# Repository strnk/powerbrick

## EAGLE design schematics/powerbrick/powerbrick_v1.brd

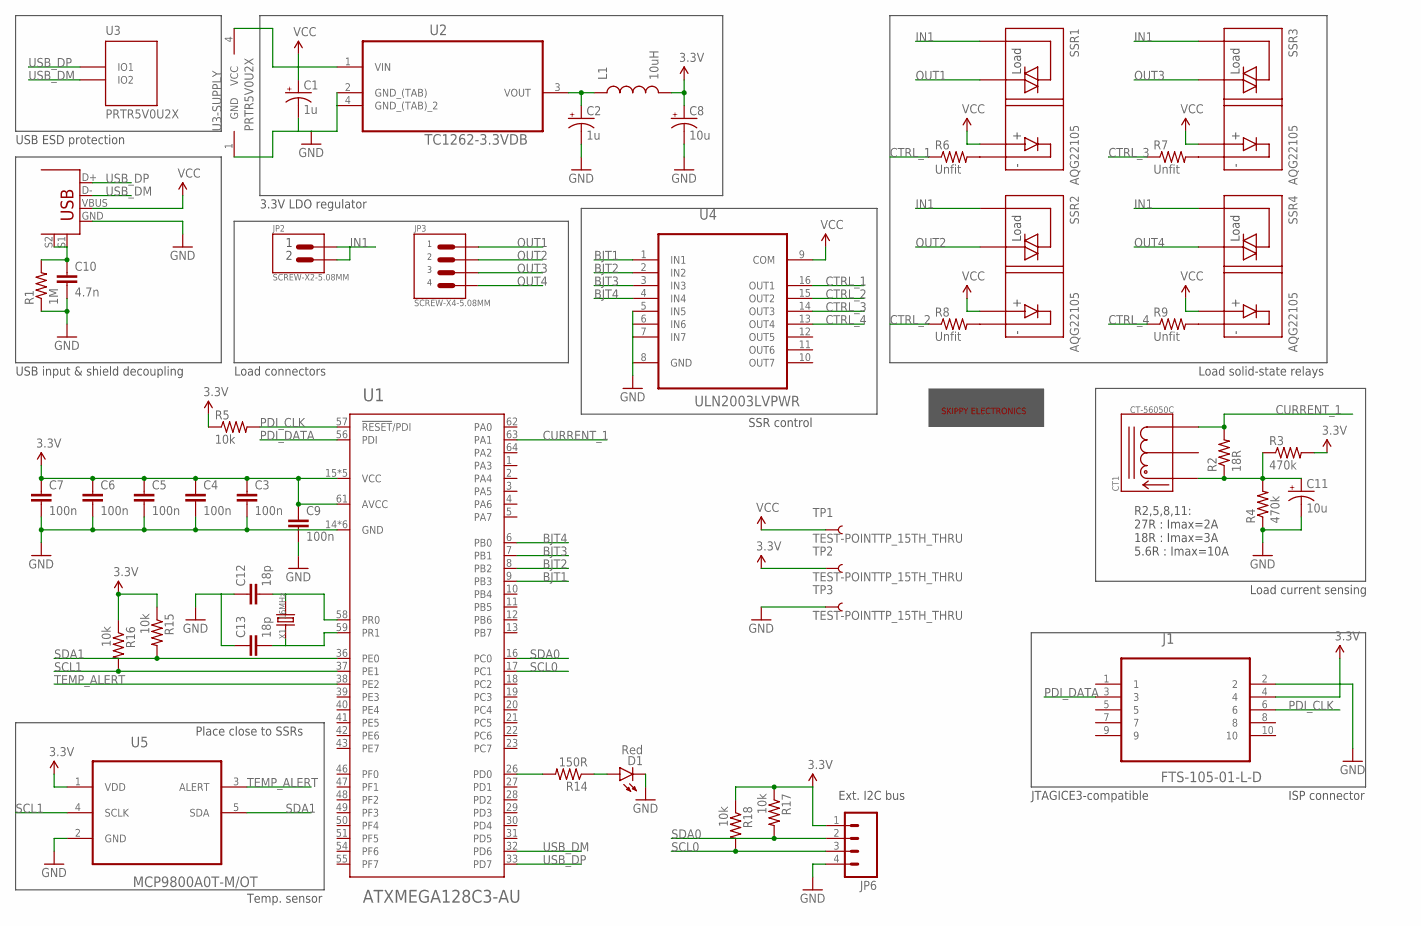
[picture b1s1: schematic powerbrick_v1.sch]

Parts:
C1, C2: 1u; EIA3216-KIT
C3, C4, C5, C6, C7, C9: 100n; 0805
C8, C11: 10u; EIA3216-KIT
C10: 4.7n; 0805
C12, C13: 18p; 0805
CT1: CT-56050C
D1: Red; LED5MM
J1: FTS-105-01-L-D; SAMTEC_FTS-105-01-L-D
JP1: USB+SHIELD; USB-B-PTH
JP2: SCREW-X2-5.08MM; 1X02-5.08MM
JP3: SCREW-X4-5.08MM; 1X04
JP6: M04POLAR_LOCK; MOLEX-1X4_LOCK
L1: 10uH; SRN6045
R1: 1M; 0805
R2: 18R; R2512
R3, R4: 470k; 0805
R5, R15, R16, R17, R18: 10k; 0805
R6, R7, R8, R9: Unfit; 0805
R14: 150R; 0805
SSR1, SSR2, SSR3, SSR4: AQG22105; SSR-100-400-300
TP1, TP2, TP3: TEST-POINTTP_15TH_THRU; TP_15TH
U1: ATXMEGA128C3-AU; TQFP-64A-64
U2: TC1262-3.3VDB; SOT230P700X180-4N
U3: PRTR5V0U2X; SOT-143B
U4: ULN2003LVPWR; SOP65P640X120-16N
U5: MCP9800A0T-M/OT; SOT95P280X145-5N
U$2: SKIPPYTXT-PLC-10MM
X1: 16MHz; HC49S

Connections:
3.3V: C3.1, C4.1, C5.1, C6.1, C7.1, C8.A (+), C9.1, J1.4, JP6.1, L1.2, R3.2, R5.1, R15.1, R16.1, R17.1, R18.1, TP2.P$1, U1.15 (VCC), U1.25 (VCC), U1.35 (VCC), U1.45 (VCC), U1.53 (VCC), U1.61 (AVCC), U5.1 (VDD)
BJT1: U1.9 (PB3), U4.1 (IN1)
BJT2: U1.8 (PB2), U4.2 (IN2)
BJT3: U1.7 (PB1), U4.3 (IN3)
BJT4: U1.6 (PB0), U4.4 (IN4)
CTRL_1: R6.1, U4.16 (OUT1)
CTRL_2: R8.1, U4.15 (OUT2)
CTRL_3: R7.1, U4.14 (OUT3)
CTRL_4: R9.1, U4.13 (OUT4)
CURRENT_1: CT1.P$3, R2.2, U1.63 (PA1)
GND: C1.C (-), C2.C (-), C3.2, C4.2, C5.2, C6.2, C7.2, C8.C (-), C9.2, C10.2, C11.C (-), C12.1, C13.1, D1.K (C), J1.2, JP1.GND, JP6.4, R1.1, R4.1, TP3.P$1, U1.14 (GND), U1.24 (GND), U1.34 (GND), U1.44 (GND), U1.52 (GND), U1.60 (GND), U2.2 (GND_(TAB)), U2.4 (GND_(TAB)_2), U3.1 (GND), U4.5 (IN5), U4.6 (IN6), U4.7 (IN7), U4.8 (GND), U5.2 (GND)
IN1: JP2.P$1, JP2.P$2, SSR1.P$4, SSR2.P$4, SSR3.P$4, SSR4.P$4
unnamed: C12.2, U1.58 (PR0), X1.2
unnamed: C2.A (+), L1.1, U2.3 (VOUT)
unnamed: C13.2, U1.59 (PR1), X1.1
unnamed: C11.A (+), CT1.P$1, R2.1, R3.1, R4.2
unnamed: C10.1, JP1.S1, JP1.S2, R1.2
unnamed: R6.2, SSR1.P$1
unnamed: R7.2, SSR3.P$1
unnamed: R9.2, SSR4.P$1
unnamed: R14.2, U1.26 (PD0)
unnamed: D1.A, R14.1
unnamed: R8.2, SSR2.P$1
OUT1: JP3.P$1, SSR1.P$3
OUT2: JP3.P$2, SSR2.P$3
OUT3: JP3.P$3, SSR3.P$3
OUT4: JP3.P$4, SSR4.P$3
PDI_CLK: J1.6, R5.2, U1.57 (!RESET!/PDI)
PDI_DATA: J1.3, U1.56 (PDI)
SCL0: JP6.3, R18.2, U1.17 (PC1)
SCL1: R16.2, U1.37 (PE1), U5.4 (SCLK)
SDA0: JP6.2, R17.2, U1.16 (PC0)
SDA1: R15.2, U1.36 (PE0), U5.5 (SDA)
TEMP_ALERT: U1.38 (PE2), U5.3 (ALERT)
USB_DM: JP1.D-, U1.32 (PD6), U3.3 (IO2)
USB_DP: JP1.D+, U1.33 (PD7), U3.2 (IO1)
VCC: C1.A (+), JP1.VBUS, SSR1.P$2, SSR2.P$2, SSR3.P$2, SSR4.P$2, TP1.P$1, U2.1 (VIN), U3.4 (VCC), U4.9 (COM)

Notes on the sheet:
USB ESD protection
USB input & shield decoupling
3.3V LDO regulator
Load connectors
Load solid-state relays
R2,5,8,11: 27R : Imax=2A 18R : Imax=3A 5.6R : Imax=10A
Load current sensing
Temp. sensor
Place close to SSRs
Ext. I2C bus
SSR control
ISP connector
JTAGICE3-compatible

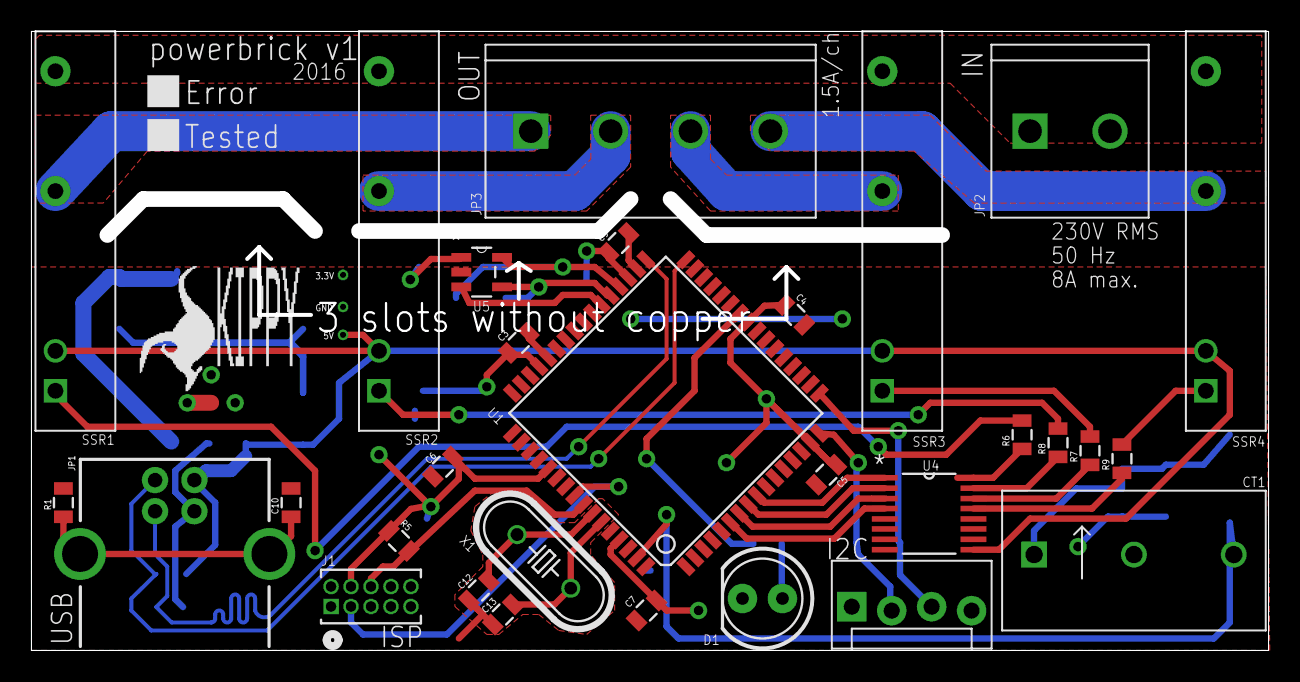
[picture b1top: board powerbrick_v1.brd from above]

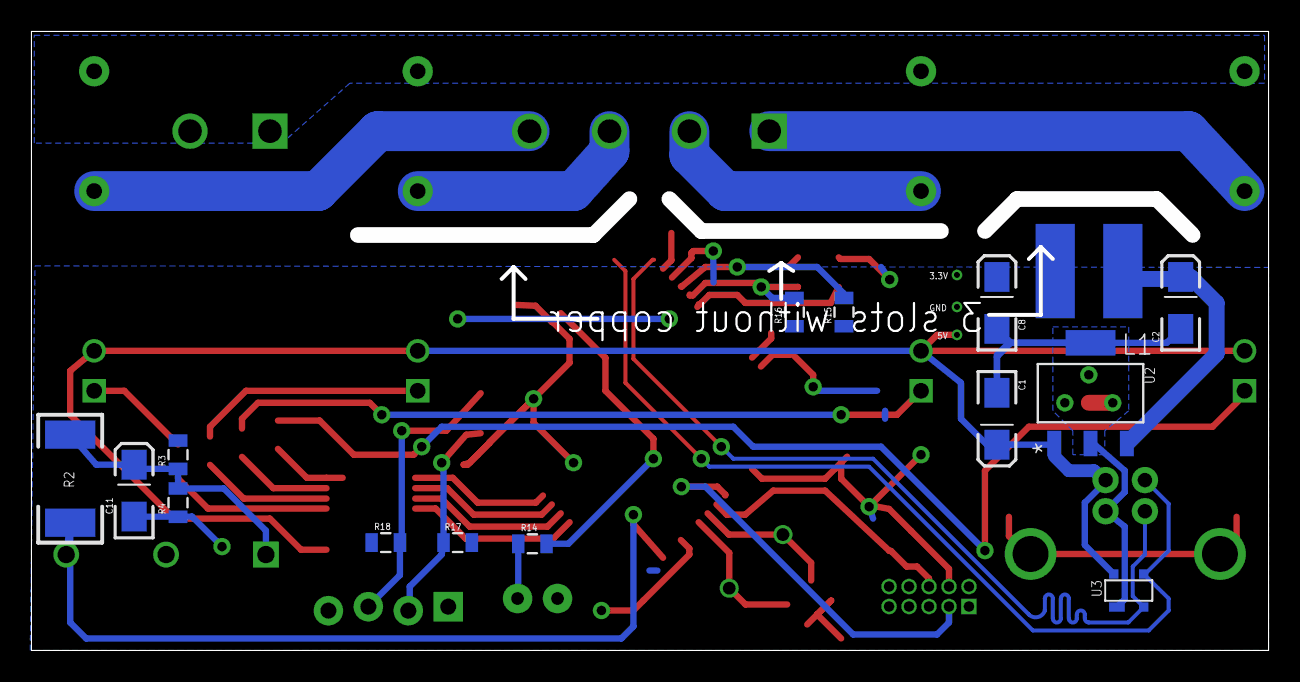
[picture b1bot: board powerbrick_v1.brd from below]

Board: 4 copper layers, 77.7 x 38.4 mm, 49 parts (15 on the bottom side), 37 nets.

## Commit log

2013-12-21 SeeedStudio libraries and motherboard schematic draft
2013-12-21 New STM32F405RGT symbol in stm32 lib
2014-01-06 Eagle library of Skippy logos
2015-02-07 Eagle lib update & logos
2015-02-08 Added Sparkfun Eagle libs
2015-02-08 Moved Sparkfun lib to 3rd-party
2015-02-08 Reorganized libs, added DC/DC buck converter and power board
2015-02-08 Inductor lib and powerboard 5V rail
2015-02-09 Power board finalized
2015-02-11 New PCB for power board
2015-02-19 Lower resolution logo for Gerber export
2015-05-03 Motherboard reference design
2015-05-04 Library refactor and motherboard update
2015-05-04 Bluetooth debug module and external boards lib. Motherboard update
2015-05-08 Motherboard v1 RTM
2016-04-06 Added 3rd-party seeedstudio and sparkfun libs
2016-04-06 Powerbrick schematic
2016-04-07 Additional docs
2016-04-07 Git ignore file
2016-04-07 Libs and drawing update
2016-04-09 Current transformer doc
2016-04-09 New parts
2016-04-09 Powerbrick schematic update
2016-04-12 Schematics update
2016-04-17 Added ISP header
2016-04-18 Replaced ISP connector - PCB draft
2016-04-19 Added test points and HV separation milling
2016-04-22 Added slots to separate power planes from mains voltage traces
2016-04-22 Powerbrick v1 RTM

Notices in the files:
parts and their libraries:
SparkFun-Connectors: Licensing: Creative Commons ShareAlike 4.0 International - https://creativecommons.org/licenses/by-sa/4.0
NXPSemiconductors: Creative Commons Attribution-ShareAlike 3.0 Unported (CC BY-SA 3.0), http://creativecommons.org/licenses/by-sa/3.0/.
